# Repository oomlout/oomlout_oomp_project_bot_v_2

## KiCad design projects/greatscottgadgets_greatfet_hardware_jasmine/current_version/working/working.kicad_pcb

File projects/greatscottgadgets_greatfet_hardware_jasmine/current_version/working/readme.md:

# greatfet_hardware
 
## summary 
* id: greatscottgadgets_greatfet_hardware_jasmine
* user: greatscottgadgets
* name: greatfet_hardware
* board: jasmine
* repo: https://github.com/greatscottgadgets/greatfet-hardware
* src_file_repo_kicad_pcb: jasmine/jasmine.kicad_pcb
* src_file_repo_kicad_pcb_link: https://github.com/greatscottgadgets/greatfet-hardware/tree/master/jasmine/jasmine.kicad_pcb

* src_file_repo_sch: jasmine/jasmine.sch
* src_file_repo_sch_link: https://github.com/greatscottgadgets/greatfet-hardware/tree/master/jasmine/jasmine.sch
* full details link: https://github.com/oomlout/oomlout_oomp_project_bot_v_2/tree/main/projects/greatscottgadgets_greatfet_hardware_jasmine/current_version/working

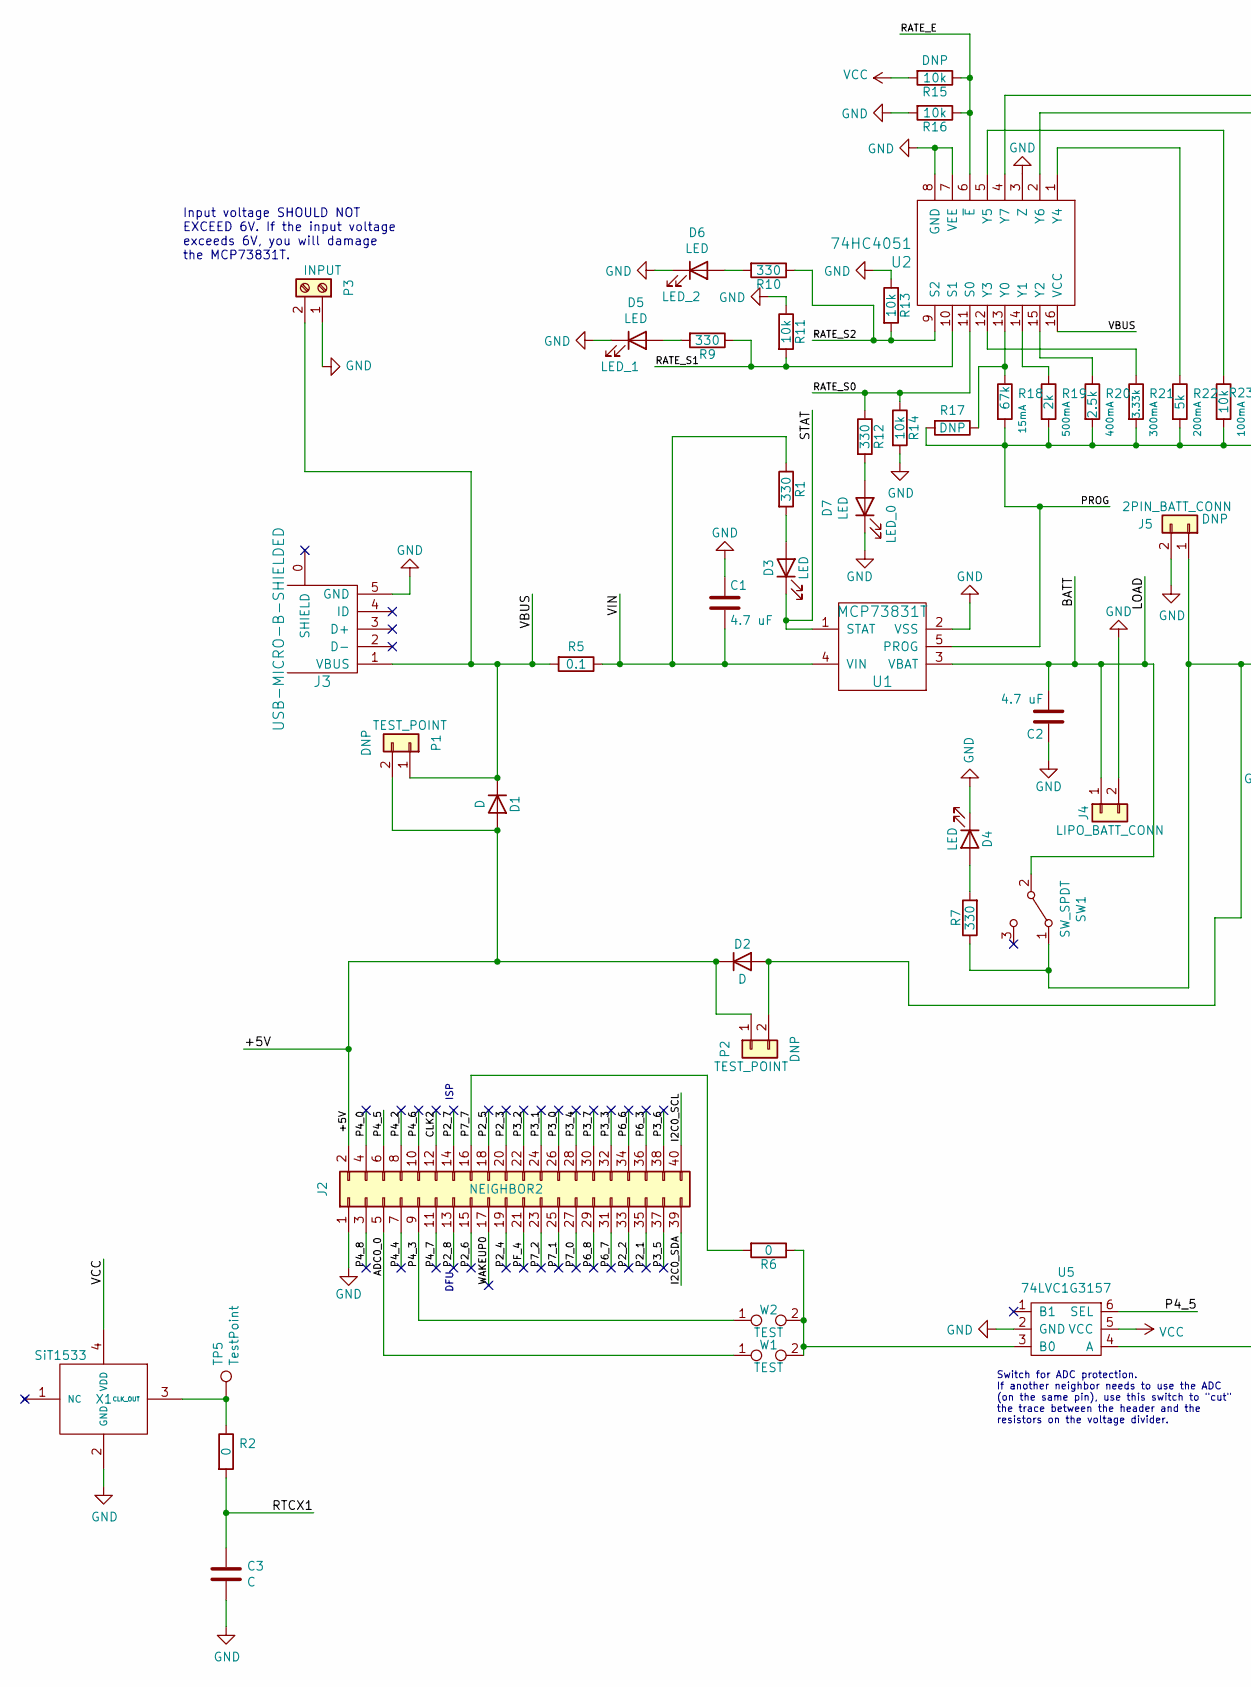
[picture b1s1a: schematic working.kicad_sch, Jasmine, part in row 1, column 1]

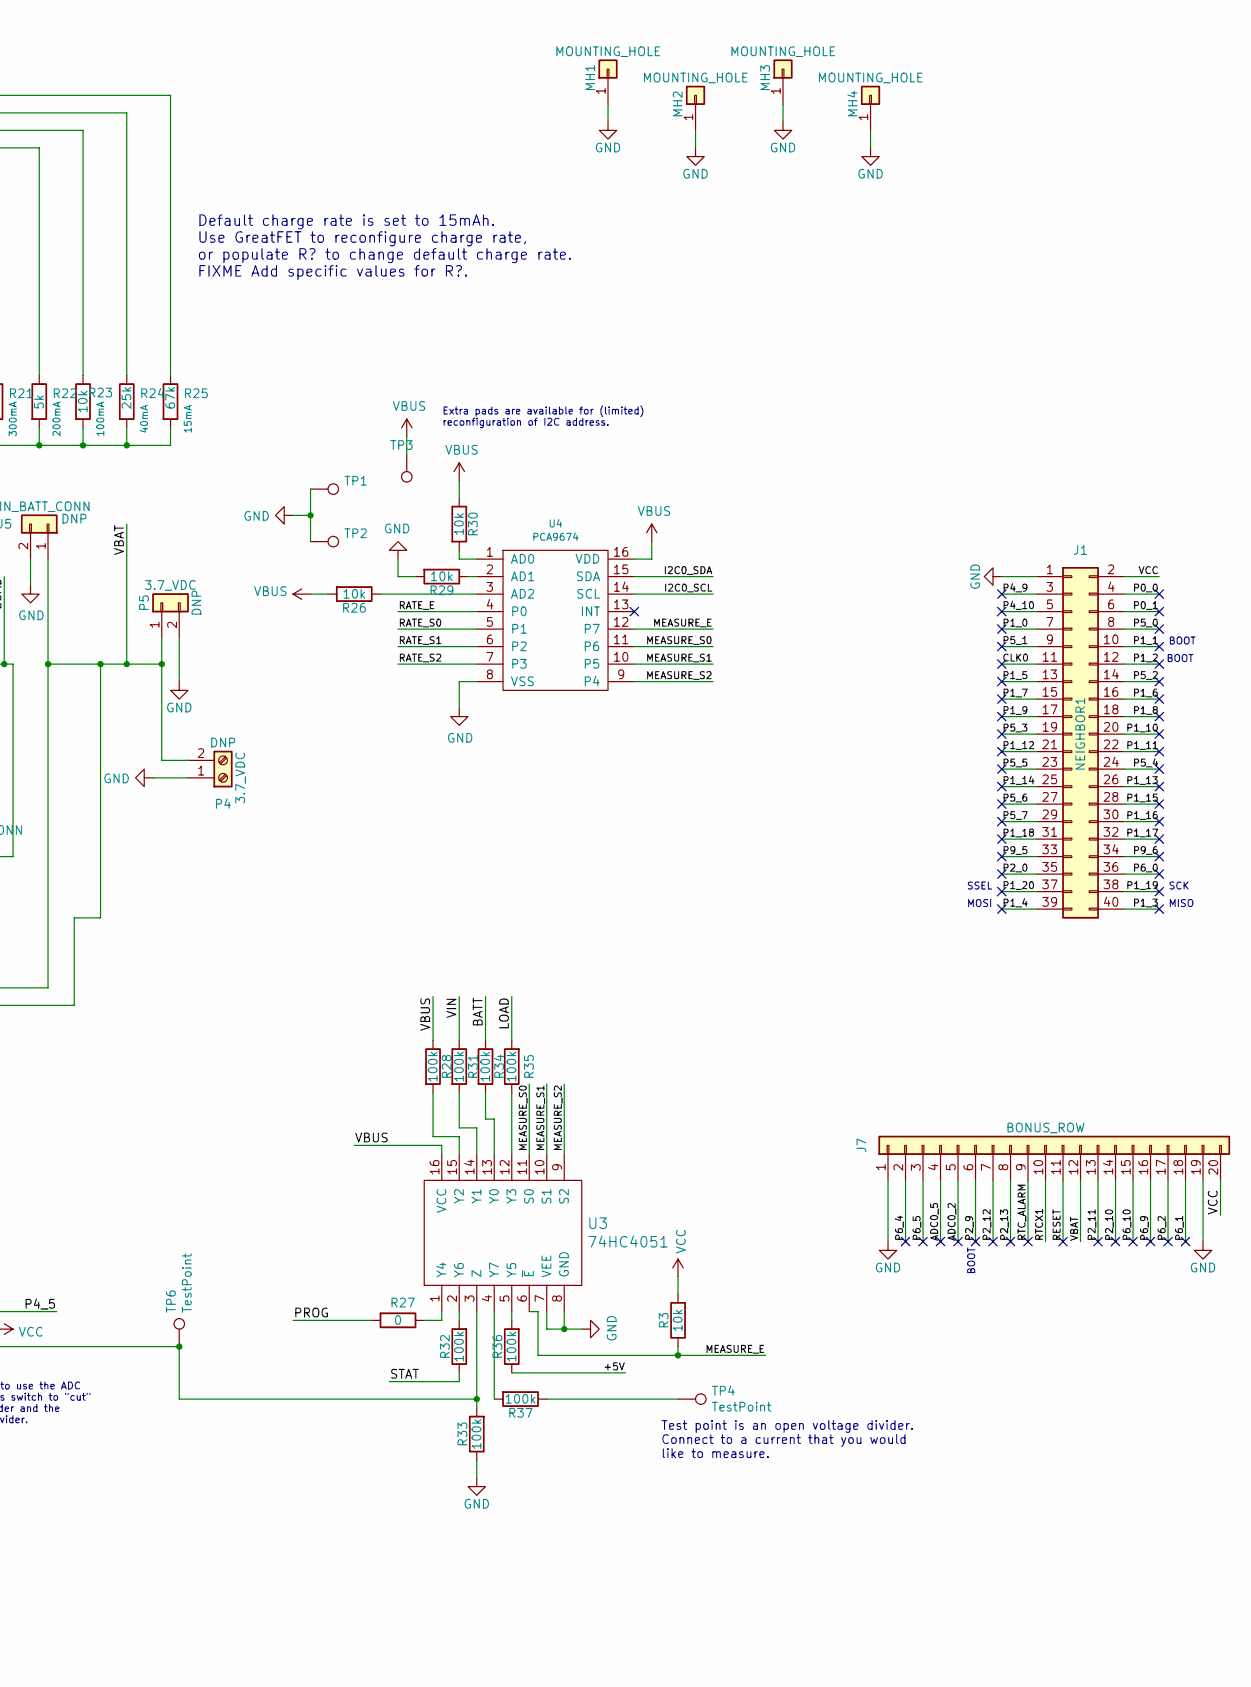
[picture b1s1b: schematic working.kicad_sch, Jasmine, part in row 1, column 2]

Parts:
C1, C2: 4.7 uF; 0603; Part Number GRM188R60J475KE19D
C3: C; 0603
D1, D2: D; SOD128; Part Number PMEG3050EP,115
D3: LED; 0603D; Part Number SML-LX0603GW-TR
D4: LED; 0603D; Part Number SML-LX0603IW-TR
D5, D6, D7: LED; 0603D; Part Number SML-D12Y8WT86
J1: NEIGHBOR1; HEADER-2x20; Part Number SSQ-120-23-G-D
J2: NEIGHBOR2; HEADER-2x20; Part Number SSQ-120-23-G-D
J3: USB-MICRO-B-SHIELDED; USB-MICROB-FCI-10103592-LONGPADS; Part Number 10103592-0001LF
J4: LIPO_BATT_CONN; JST_PH_S2B-PH-SM4-TB_02x2.00mm_Angled; Part Number S2B-PH-SM4-TB(LF)(SN)
J5: 2PIN_BATT_CONN; JST_PH_S2B-PH-SM4-TB_02x2.00mm_Angled; Part Number S2B-PH-SM4-TB(LF)(SN)
J7: BONUS_ROW; HEADER-1x20; Part Number SSQ-120-23-G-S
MH1, MH2, MH3, MH4: MOUNTING_HOLE; HOLE126MIL-COPPER
P1, P2: TEST_POINT; HEADER-1x2; Part Number TSW-102-07-F-S
P3: INPUT; TerminalBlock_4UCON_19963_02x3.5mm_Straight; Part Number OSTTE020104
P4: 3.7_VDC; TerminalBlock_4UCON_19963_02x3.5mm_Straight; Part Number OSTTE020104
P5: 3.7_VDC; HEADER-1x2
R1, R9, R10, R12: 330; 0603; Part Number RMCF0603FT330R
R2, R27: 0; 0603; Part Number RMCF0603ZT0R00
R3, R11, R13, R14, R15, R16, R23, R26, R29, R30: 10k; 0603; Part Number RNCP0603FTD10K0
R5: 0.1; 0603; Part Number ERJ-3RSFR10V
R6: 0; 0603; Part Number RC0603JR-070RL
R7: 330; 0603; Part Number RMCF0603JT330R
R17: R; RESISTOR-AXIAL-2.3x6.0mm
R18, R25: 67k; 0603; Part Number RMCF0603FT66K5
R19: 2k; 0603; Part Number RMCF0603FT2K00
R20: 2.5k; 0603; Part Number RMCF0603FT2K49
R21: 3.33k; 0603; Part Number RMCF0603FG3K32
R22: 5k; 0603; Part Number RMCF0603FT4K99
R24: 25k; 0603; Part Number RMCF0603FT24K9
R28, R31, R32, R33, R34, R35, R36, R37: 100k; 0603; Part Number RMCF0603FG100K
SW1: SW_SPDT; MHSS1105; Part Number MHSS1105
TP1, TP2, TP3: 1Pin_0603
TP4, TP5, TP6: TestPoint; TESTPOINT-50MIL
U1: MCP73831T; SOT-23-5; Part Number MCP73831T-2ACI/OT
U2, U3: 74HC4051; SOIC16; Part Number 74HC4051D,653
U4: PCA9674; TSSOP16; Part Number PCA9674PW,118
U5: 74LVC1G3157; SOT363; Part Number 74LVC1G3157DW-7
W1, W2: TEST; 0603-JUMPER
X1: SiT1533; Part Number SIT1533AI-H4-AA2-32.768G

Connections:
/+5V: D1.2 (A), D2.1 (K), J2.2, P1.2, P2.1, R36.1
/ADC0_0: J2.5, W1.1
/ADC0_2: J7.5
/ADC0_5: J7.4
/BATT: C2.2, J4.1, R34.1, R35.2, SW1.2 (B), U1.3 (VBAT)
/CLK0: J1.11
/CLK2: J2.12
/I2C0_SCL: J2.40, U4.14 (SCL)
/I2C0_SDA: J2.39, U4.15 (SDA)
/MEASURE_E: R3.1, U3.6 (~E), U4.12 (P7)
/MEASURE_S0: U3.11 (S0), U4.11 (P6)
/MEASURE_S1: U3.10 (S1), U4.10 (P5)
/MEASURE_S2: U3.9 (S2), U4.9 (P4)
/P0_0: J1.4
/P0_1: J1.6
/P1_0: J1.7
/P1_1: J1.10
/P1_2: J1.12
/P1_3: J1.40
/P1_4: J1.39
/P1_5: J1.13
/P1_6: J1.16
/P1_7: J1.15
/P1_8: J1.18
/P1_9: J1.17
/P1_10: J1.20
/P1_11: J1.22
/P1_12: J1.21
/P1_13: J1.26
/P1_14: J1.25
/P1_15: J1.28
/P1_16: J1.30
/P1_17: J1.32
/P1_18: J1.31
/P1_19: J1.38
/P1_20: J1.37
/P2_0: J1.35
/P2_1: J2.35
/P2_2: J2.33
/P2_3: J2.20
/P2_4: J2.19
/P2_5: J2.18
/P2_6: J2.15
/P2_7: J2.14
/P2_8: J2.13
/P2_9: J7.6
/P2_10: J7.14
/P2_11: J7.13
/P2_12: J7.7
/P2_13: J7.8
/P3_0: J2.26
/P3_1: J2.24
/P3_2: J2.22
/P3_3: J2.32
/P3_4: J2.28
/P3_5: J2.37
/P3_6: J2.38
/P3_7: J2.30
/P4_0: J2.4
/P4_2: J2.8
/P4_3: J2.9, W2.1
/P4_4: J2.7
/P4_5: J2.6, U5.6 (SEL)
/P4_6: J2.10
/P4_7: J2.11
/P4_8: J2.3
/P4_9: J1.3
/P4_10: J1.5
/P5_0: J1.8
/P5_1: J1.9
/P5_2: J1.14
/P5_3: J1.19
/P5_4: J1.24
/P5_5: J1.23
/P5_6: J1.27
/P5_7: J1.29
/P6_0: J1.36
/P6_1: J7.18
/P6_2: J7.17
/P6_3: J2.36
/P6_4: J7.2
/P6_5: J7.3
/P6_6: J2.34
/P6_7: J2.31
/P6_8: J2.29
/P6_9: J7.16
/P6_10: J7.15
/P7_0: J2.27
/P7_1: J2.25
/P7_2: J2.23
/P7_7: J2.16, R6.2
/P9_5: J1.33
/P9_6: J1.34
/PF_4: J2.21
/PROG: R17.2, R18.2, R19.2, R20.2, R21.2, R22.2, R23.2, R24.2, R25.2, R27.2, U1.5 (PROG)
/RATE_E: R15.1, R16.1, U2.6 (~E), U4.4 (P0)
/RATE_S0: R12.1, R14.1, U2.11 (S0), U4.5 (P1)
/RATE_S1: R9.1, R11.2, U2.10 (S1), U4.6 (P2)
/RATE_S2: R10.1, R13.2, U2.9 (S2), U4.7 (P3)
/RESET: J7.11
/RTCX1: C3.1, J7.10, R2.2
/RTC_ALARM: J7.9
/STAT: D3.1 (K), R32.1, U1.1 (STAT)
/VBAT: D2.2 (A), J5.1, J7.12, P2.2, P4.2, P5.1, R7.1, SW1.1 (A)
/VIN: C1.2, R1.1, R5.1, R31.1, U1.4 (VIN)
/WAKEUP0: J2.17
GND: C1.1, C2.1, C3.2, D4.1 (K), D5.1 (K), D6.1 (K), D7.1 (K), J1.1, J2.1, J3.5 (GND), J4.2, J5.2, J7.1, J7.19, MH1.1, MH2.1, MH3.1, MH4.1, P3.1, P4.1, P5.2, R11.1, R13.1, R14.2, R16.2, R29.2, R33.1, TP1.1, TP2.1, U1.2 (VSS), U2.3 (Z), U2.7 (VEE), U2.8 (GND), U3.7 (VEE), U3.8 (GND), U4.8 (VSS), U5.2 (GND), X1.2 (GND)
unnamed: D3.2 (A), R1.2
unnamed: D4.2 (A), R7.2
unnamed: D5.2 (A), R9.2
unnamed: D6.2 (A), R10.2
unnamed: D7.2 (A), R12.2
unnamed: R2.1, TP5.1, X1.3 (CLK_OUT)
unnamed: R6.1, U5.3 (B0), W1.2, W2.2
unnamed: R17.1, R18.1, U2.13 (Y0)
unnamed: R19.1, U2.14 (Y1)
unnamed: R20.1, U2.15 (Y2)
unnamed: R21.1, U2.12 (Y3)
unnamed: R22.1, U2.1 (Y4)
unnamed: R23.1, U2.5 (Y5)
unnamed: R24.1, U2.2 (Y6)
unnamed: R25.1, U2.4 (Y7)
unnamed: R26.1, U4.3 (AD2)
unnamed: R27.1, U3.1 (Y4)
unnamed: R28.2, U3.15 (Y2)
unnamed: R29.1, U4.2 (AD1)
unnamed: R30.2, U4.1 (AD0)
unnamed: R31.2, U3.14 (Y1)
unnamed: R32.2, U3.2 (Y6)
unnamed: R33.2, TP6.1, U3.3 (Z), U5.4 (A)
unnamed: R34.2, U3.13 (Y0)
unnamed: R35.1, U3.12 (Y3)
unnamed: R36.2, U3.5 (Y5)
unnamed: R37.1, TP4.1
unnamed: R37.2, U3.4 (Y7)
VBUS: D1.1 (K), J3.1 (VBUS), P1.1, P3.2, R5.2, R26.2, R28.1, R30.1, TP3.1, U2.16 (VCC), U3.16 (VCC), U4.16 (VDD)
VCC: J1.2, J7.20, R3.2, R15.2, U5.5 (VCC), X1.4 (VDD)

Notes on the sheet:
Input voltage SHOULD NOT EXCEED 6V. If the input voltage exceeds 6V, you will damage the MCP73831T.
Default charge rate is set to 15mAh. Use GreatFET to reconfigure charge rate, or populate R? to change default charge rate. FIXME Add specific values for R?.
Extra pads are available for (limited) reconfiguration of I2C address.
Switch for ADC protection. If another neighbor needs to use the ADC (on the same pin), use this switch to "cut" the trace between the header and the resistors on the voltage divider.
MISO
SCK
Test point is an open voltage divider. Connect to a current that you would like to measure.
BOOT
MOSI
ISP
DFU
SSEL

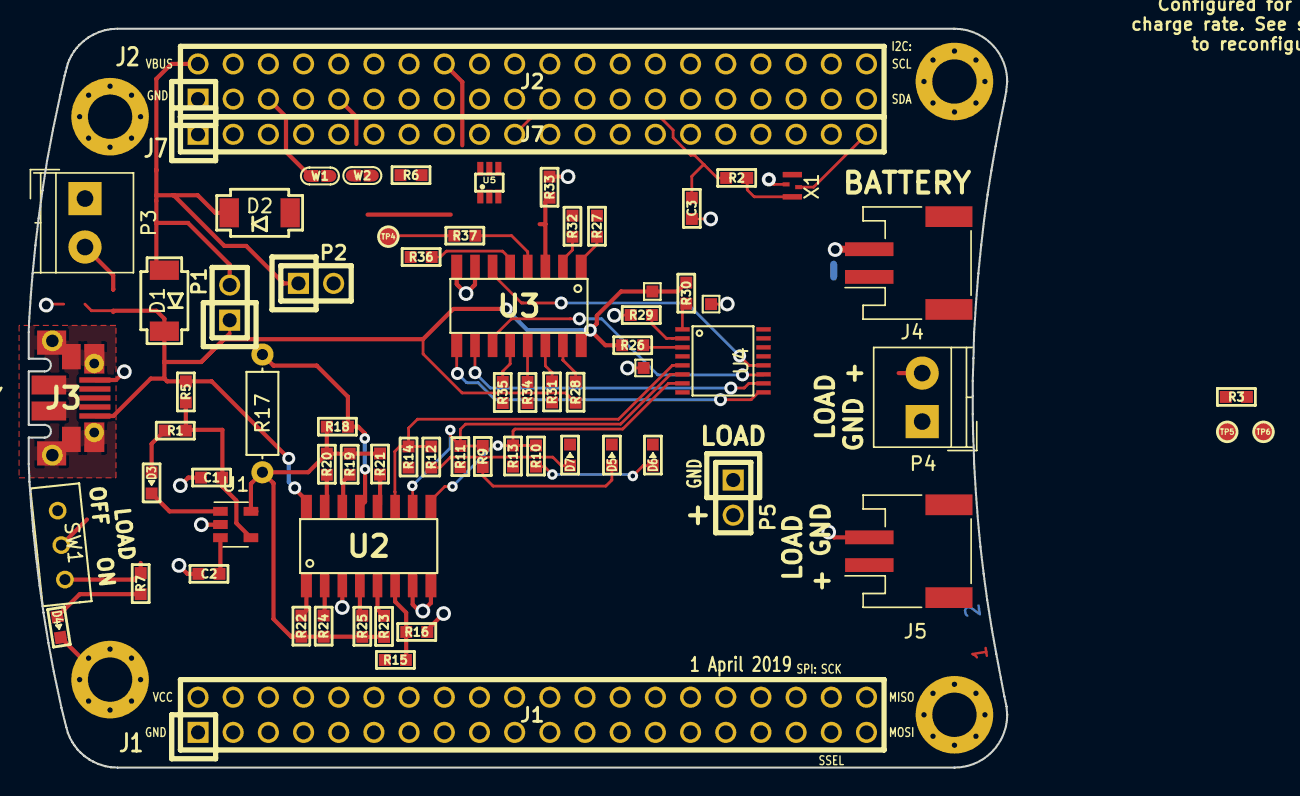
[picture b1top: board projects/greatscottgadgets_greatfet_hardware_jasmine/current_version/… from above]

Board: 2 copper layers, 70.6 x 53.3 mm, 75 parts (0 on the bottom side), 52 nets.

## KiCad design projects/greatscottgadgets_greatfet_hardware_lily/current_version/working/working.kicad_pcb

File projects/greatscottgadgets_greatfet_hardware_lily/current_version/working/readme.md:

# greatfet_hardware
 
## summary 
* id: greatscottgadgets_greatfet_hardware_lily
* user: greatscottgadgets
* name: greatfet_hardware
* board: lily
* repo: https://github.com/greatscottgadgets/greatfet-hardware
* src_file_repo_kicad_pcb: lily/lily.kicad_pcb
* src_file_repo_kicad_pcb_link: https://github.com/greatscottgadgets/greatfet-hardware/tree/master/lily/lily.kicad_pcb

* src_file_repo_sch: lily/lily.sch
* src_file_repo_sch_link: https://github.com/greatscottgadgets/greatfet-hardware/tree/master/lily/lily.sch
* full details link: https://github.com/oomlout/oomlout_oomp_project_bot_v_2/tree/main/projects/greatscottgadgets_greatfet_hardware_lily/current_version/working

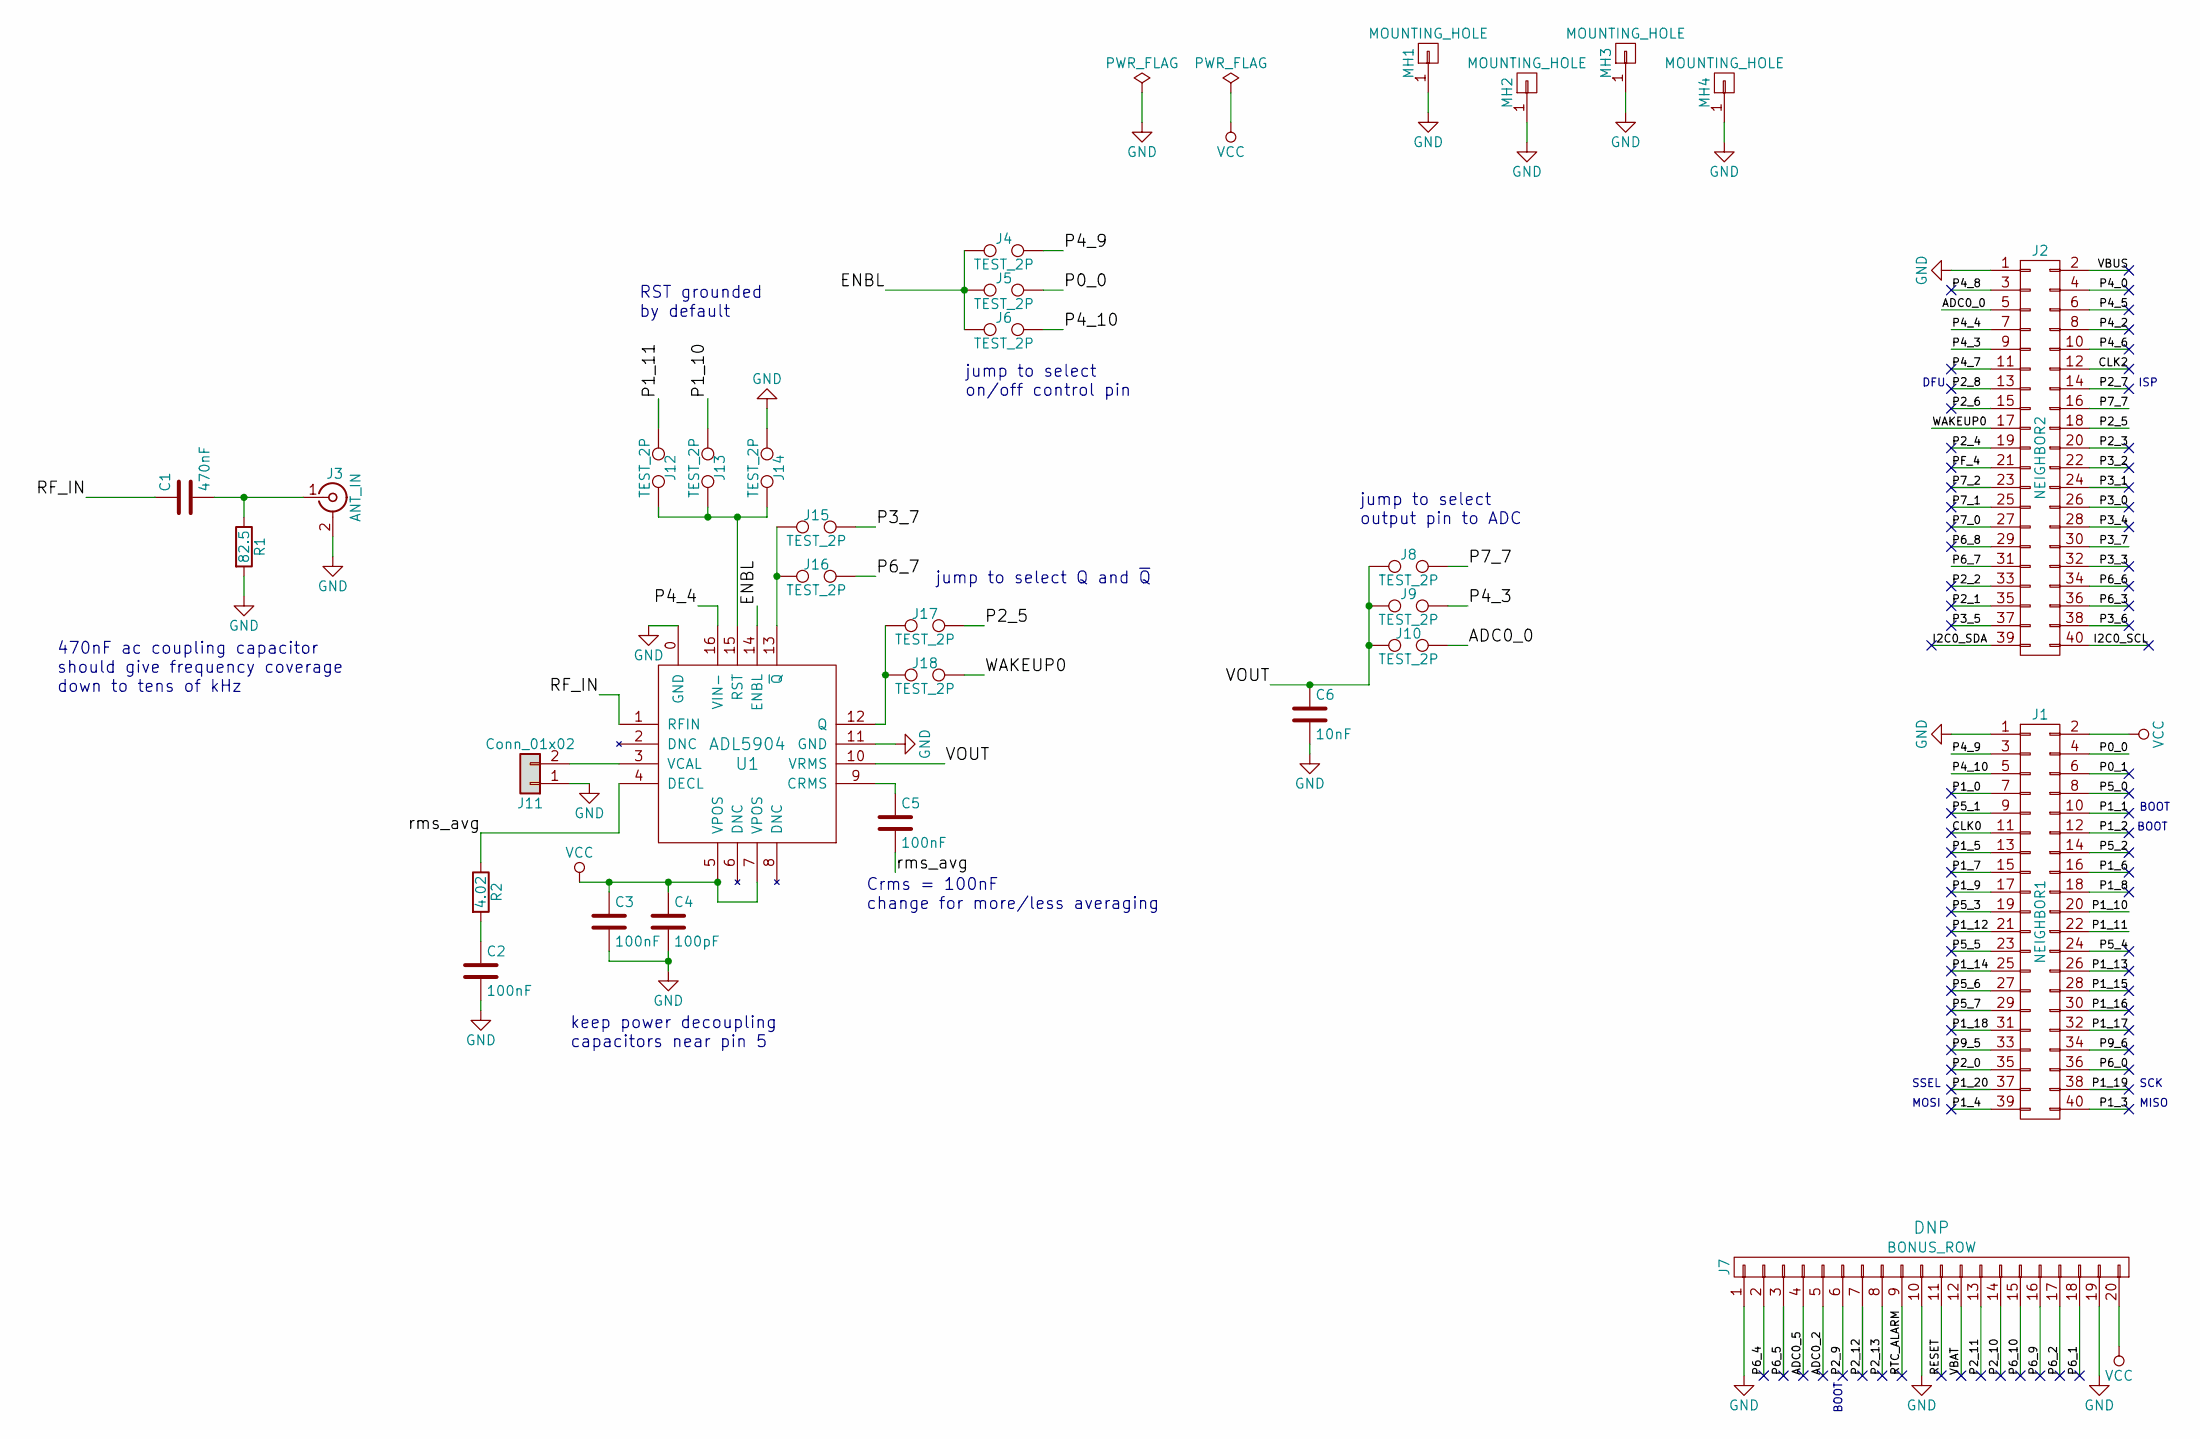
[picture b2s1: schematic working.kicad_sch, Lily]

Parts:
C1: 470nF; 0603; Part Number GRM188R61H474KA12D
C2, C3, C5: 100nF; 0603; Part Number GCM188L81H104KA57D
C4: 100pF; 0603; Part Number GQM1885C1H101JB01D
C6: 10nF; 0603; Part Number 885012206065
J1: NEIGHBOR1; HEADER-2x20; Part Number SSQ-120-23-G-D
J2: NEIGHBOR2; HEADER-2x20; Part Number SSQ-120-23-G-D
J3: ANT_IN; SMA-EDGE; Part Number CONREVSMA003.031
J4, J5, J6, J8, J9, J10, J12, J13, J14, J15, J16, J17, J18: TEST_2P; 0603-JUMPER
J7: BONUS_ROW; HEADER-1x20; Part Number SSQ-120-23-G-S
J11: Conn_01x02; Pin_Header_Straight_1x02_Pitch2.54mm
MH1, MH2, MH3, MH4: MOUNTING_HOLE; HOLE126MIL-COPPER
R1: 82.5; 0603; Part Number RMCF0603FT82R5
R2: 4.02; 0603; Part Number RMCF0603FT4R02
U1: ADL5904; QFN16-3; Part Number ADL5904ACPZN-R7

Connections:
/ADC0_0: J2.5, J10.2
/ADC0_2: J7.5
/ADC0_5: J7.4
/CLK0: J1.11
/CLK2: J2.12
/ENBL: J4.1, J5.1, J6.1, U1.14 (ENBL)
/I2C0_SCL: J2.40
/I2C0_SDA: J2.39
/P0_0: J1.4, J5.2
/P0_1: J1.6
/P1_0: J1.7
/P1_1: J1.10
/P1_2: J1.12
/P1_3: J1.40
/P1_4: J1.39
/P1_5: J1.13
/P1_6: J1.16
/P1_7: J1.15
/P1_8: J1.18
/P1_9: J1.17
/P1_10: J1.20, J13.1
/P1_11: J1.22, J12.1
/P1_12: J1.21
/P1_13: J1.26
/P1_14: J1.25
/P1_15: J1.28
/P1_16: J1.30
/P1_17: J1.32
/P1_18: J1.31
/P1_19: J1.38
/P1_20: J1.37
/P2_0: J1.35
/P2_1: J2.35
/P2_2: J2.33
/P2_3: J2.20
/P2_4: J2.19
/P2_5: J2.18, J17.2
/P2_6: J2.15
/P2_7: J2.14
/P2_8: J2.13
/P2_9: J7.6
/P2_10: J7.14
/P2_11: J7.13
/P2_12: J7.7
/P2_13: J7.8
/P3_0: J2.26
/P3_1: J2.24
/P3_2: J2.22
/P3_3: J2.32
/P3_4: J2.28
/P3_5: J2.37
/P3_6: J2.38
/P3_7: J2.30, J15.2
/P4_0: J2.4
/P4_2: J2.8
/P4_3: J2.9, J9.2
/P4_4: J2.7, U1.16 (VIN-)
/P4_5: J2.6
/P4_6: J2.10
/P4_7: J2.11
/P4_8: J2.3
/P4_9: J1.3, J4.2
/P4_10: J1.5, J6.2
/P5_0: J1.8
/P5_1: J1.9
/P5_2: J1.14
/P5_3: J1.19
/P5_4: J1.24
/P5_5: J1.23
/P5_6: J1.27
/P5_7: J1.29
/P6_0: J1.36
/P6_1: J7.18
/P6_2: J7.17
/P6_3: J2.36
/P6_4: J7.2
/P6_5: J7.3
/P6_6: J2.34
/P6_7: J2.31, J16.2
/P6_8: J2.29
/P6_9: J7.16
/P6_10: J7.15
/P7_0: J2.27
/P7_1: J2.25
/P7_2: J2.23
/P7_7: J2.16, J8.2
/P9_5: J1.33
/P9_6: J1.34
/PF_4: J2.21
/RESET: J7.11
/RF_IN: C1.1, U1.1 (RFIN)
/RTC_ALARM: J7.9
/VBAT: J7.12
/VBUS: J2.2
/VOUT: C6.1, J8.1, J9.1, J10.1, U1.10 (VRMS)
/WAKEUP0: J2.17, J18.2
/rms_avg: C5.2, R2.1, U1.4 (DECL)
GND: C2.2, C3.2, C4.2, C6.2, J1.1, J2.1, J3.2 (Ext), J7.1, J7.10, J7.19, J11.1, J14.1, MH1.1, MH2.1, MH3.1, MH4.1, R1.2, U1.0 (GND), U1.11 (GND)
unnamed: C1.2, J3.1 (In), R1.1
unnamed: C2.1, R2.2
unnamed: C5.1, U1.9 (CRMS)
unnamed: J11.2, U1.3 (VCAL)
unnamed: J12.2, J13.2, J14.2, U1.15 (RST)
unnamed: J15.1, J16.1, U1.13 (~Q)
unnamed: J17.1, J18.1, U1.12 (Q)
VCC: C3.1, C4.1, J1.2, J7.20, U1.5 (VPOS), U1.7 (VPOS)

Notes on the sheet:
BOOT
jump to select on/off control pin
jump to select output pin to ADC
MISO
keep power decoupling capacitors near pin 5
jump to select Q and ~{Q}
SSEL
470nF ac coupling capacitor should give frequency coverage down to tens of kHz
MOSI
RST grounded by default
ISP
Crms = 100nF change for more/less averaging
DFU
SCK

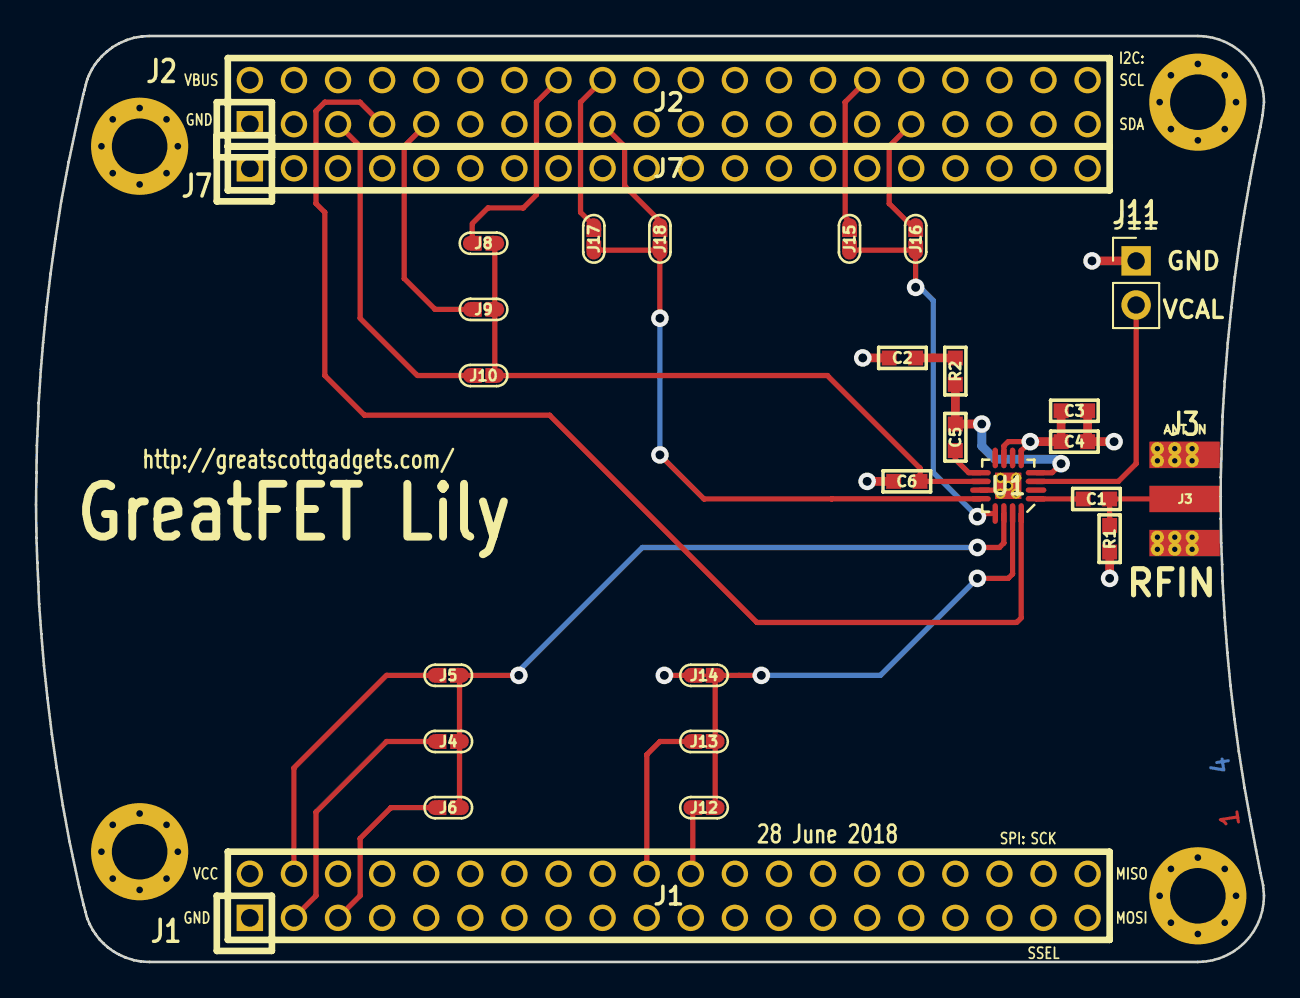
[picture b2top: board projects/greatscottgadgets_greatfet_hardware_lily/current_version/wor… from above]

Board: 4 copper layers, 70.7 x 53.3 mm, 31 parts (0 on the bottom side), 26 nets.

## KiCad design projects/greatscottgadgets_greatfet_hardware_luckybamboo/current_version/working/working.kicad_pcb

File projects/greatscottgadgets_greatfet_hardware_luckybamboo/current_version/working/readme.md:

# greatfet_hardware
 
## summary 
* id: greatscottgadgets_greatfet_hardware_luckybamboo
* user: greatscottgadgets
* name: greatfet_hardware
* board: luckybamboo
* repo: https://github.com/greatscottgadgets/greatfet-hardware
* src_file_repo_kicad_pcb: luckybamboo/luckybamboo.kicad_pcb
* src_file_repo_kicad_pcb_link: https://github.com/greatscottgadgets/greatfet-hardware/tree/master/luckybamboo/luckybamboo.kicad_pcb

* src_file_repo_sch: luckybamboo/luckybamboo.sch
* src_file_repo_sch_link: https://github.com/greatscottgadgets/greatfet-hardware/tree/master/luckybamboo/luckybamboo.sch
* full details link: https://github.com/oomlout/oomlout_oomp_project_bot_v_2/tree/main/projects/greatscottgadgets_greatfet_hardware_luckybamboo/current_version/working

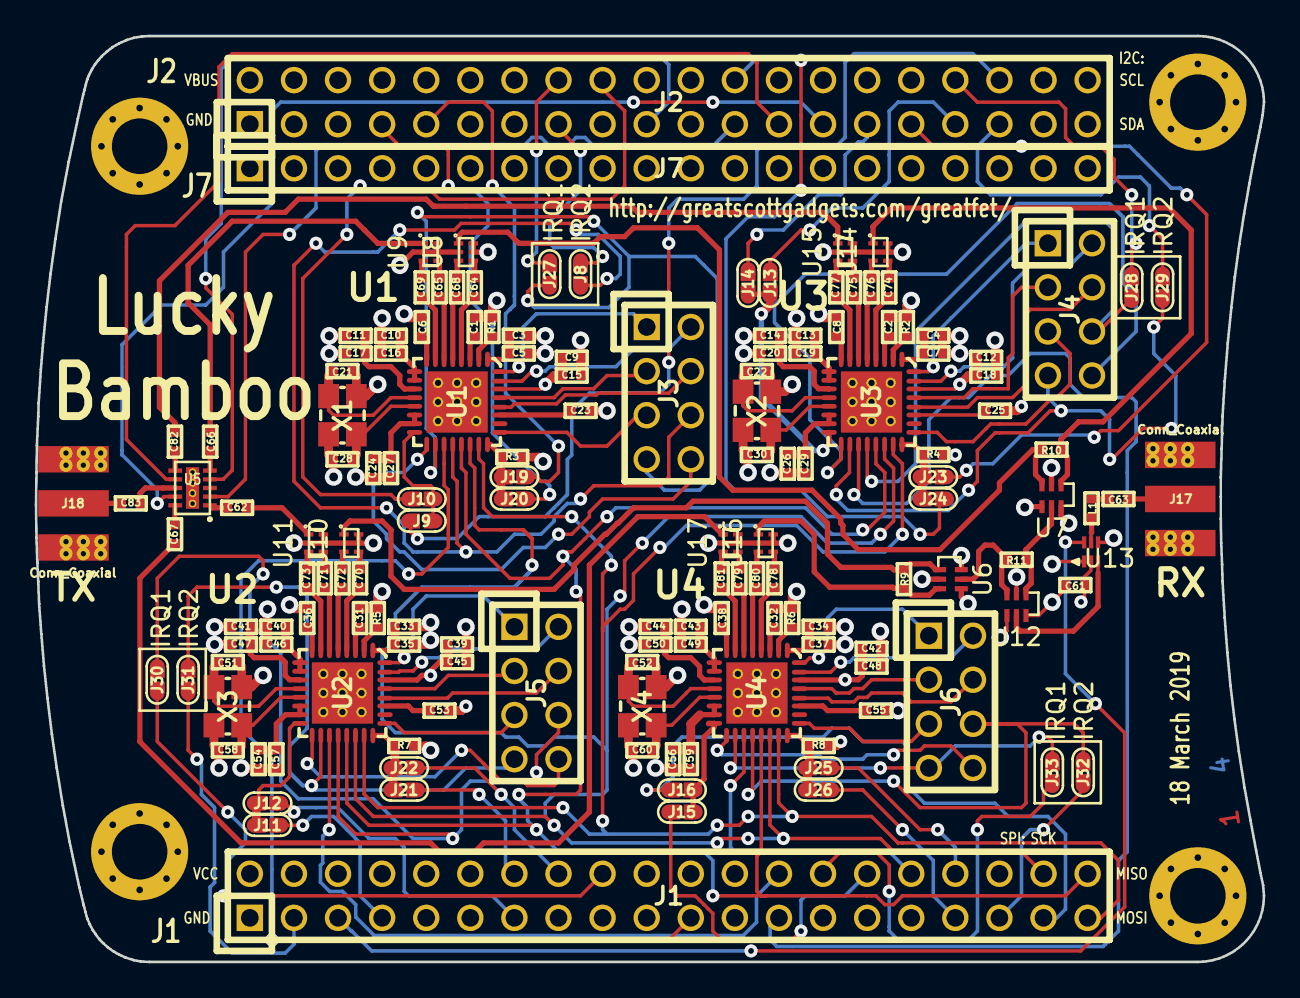
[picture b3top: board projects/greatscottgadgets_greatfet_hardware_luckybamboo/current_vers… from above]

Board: 4 copper layers, 70.7 x 53.3 mm, 153 parts (0 on the bottom side), 170 nets.

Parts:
C1, C2, C6, C8, C31, C32, C36, C38: 100pF; 0402
C3, C4, C9, C10, C11, C12, C13, C14, C24, C26, C33, C34, C39, C40, C41, C42, C43, C44, C54, C56: 220nF; 0402
C5, C7, C15, C16, C17, C18, C19, C20, C27, C29, C35, C37, C45, C46, C47, C48, C49, C50, C57, C59: 27pF; 0402
C21, C22, C28, C30, C51, C52, C58, C60: 18pF; 0402
C23, C25, C53, C55, C61, C63: 1nF; 0402
C62, C66, C67, C82, C83: 47pF; 0402
C64, C65, C68, C69, C70, C71, C72, C73, C74, C75, C76, C77, C78, C79, C80, C81: 10nF; 0402
J1: NEIGHBOR1; HEADER-2x20
J2: NEIGHBOR2; HEADER-2x20
J3, J4, J5, J6: Conn_01x08; HEADER-2x4
J7: BONUS_ROW; HEADER-1x20
J8, J9, J10, J11, J12, J13, J14, J15, J16, J19, J20, J21, J22, J23, J24, J25, J26, J27, J28, J29, J30, J31, J32, J33: TEST_2P; 0603-JUMPER
J17, J18: Conn_Coaxial; SMA-EDGE
L1: 3.8nH; 0402
MH1, MH2, MH3, MH4: MOUNTING_HOLE; HOLE126MIL-COPPER
R1, R2, R5, R6: 27k; 0402
R3, R4, R7, R8: 10k; 0402
R9, R10, R11: 100; 0402
U1, U2, U3, U4: ADF7242; LFCSP32
U5: SKY13322; SKY13322-375LF
U6, U7, U12: HHM2293A1
U8, U9, U10, U11, U14, U15, U16, U17: ADF7242_balun
U13: BGA7H1N6
X1, X2, X3, X4: XTAL4PIN; XTAL3.2x2.5mm

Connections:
/DR1: J9.1, J10.1, U1.16
/DR2: J11.1, J12.1, U2.16
/DR3: J13.1, J14.1, U3.16
/DR4: J15.1, J16.1, U4.16
/DT1: J3.8, U1.17
/DT2: J5.8, U2.17
/DT3: J4.8, U3.17
/DT4: J6.8, U4.17
/IRQ1: J3.6, J8.2, U1.20
/IRQ2: J5.6, J30.2, U2.20
/IRQ3: J4.6, J28.2, U3.20
/IRQ4: J6.6, J32.2, U4.20
/P1_0: J1.7, J11.2
/P1_3: J1.40, U1.21, U2.21, U3.21, U4.21
/P1_4: J1.39, U1.23, U2.23, U3.23, U4.23
/P1_5: J1.13, J12.2
/P1_6: J1.16, J22.2
/P1_8: J1.18, J30.1
/P1_12: J1.21, U1.19
/P1_13: J1.26, U2.19
/P1_14: J1.25, U3.19
/P1_15: J1.28, J33.1
/P1_16: J1.30, J15.2
/P1_17: J1.32, U4.19
/P1_19: J1.38, U1.22, U2.22, U3.22, U4.22
/P1_20: J1.37, J16.2
/P2_0: J1.35, J32.1
/P2_1: J2.35, J29.1
/P2_2: J2.33, J13.2
/P2_4: J2.19, U5.4
/P2_5: J2.18, J10.2
/P2_6: J2.15, J8.1
/P3_1: J2.24, J24.2
/P4_3: J2.9, J19.2
/P4_4: J2.7, J20.2
/P4_9: J1.3, J31.1
/P4_10: J1.5, U13.6
/P5_2: J1.14, J21.2
/P6_3: J2.36, J9.2
/P6_6: J2.34, J28.1
/P6_7: J2.31, J23.2
/P6_8: J2.29, J14.2
/P7_0: J2.27, U5.9
/P7_1: J2.25, U5.7
/P7_2: J2.23, U5.2
/P7_7: J2.16, J27.1
/P9_5: J1.33, J26.2
/P9_6: J1.34, J25.2
/PABIAOP1: J3.1, U1.32
/PABIAOP2: J5.1, U2.32
/PABIAOP3: J4.1, U3.32
/PABIAOP4: J6.1, U4.32
/PAVSUP1: J3.2, U1.31
/PAVSUP2: J5.2, U2.31
/PAVSUP3: J4.2, U3.31
/PAVSUP4: J6.2, U4.31
/RFIN: L1.1, U13.5
/RFIN1: R10.1, U7.3, U8.1
/RFIN1_N: C68.2, U1.5
/RFIN1_P: C64.2, U1.4
/RFIN2: R9.2, U6.1, U10.1
/RFIN2_N: C72.2, U2.5
/RFIN2_P: C70.2, U2.4
/RFIN3: R10.2, U7.1, U14.1
/RFIN3_N: C76.2, U3.5
/RFIN3_P: C74.2, U3.4
/RFIN4: R9.1, U6.3, U16.1
/RFIN4_N: C80.2, U4.5
/RFIN4_P: C78.2, U4.4
/RFOUT1: C66.2, U9.1
/RFOUT1_N: C69.2, U1.7
/RFOUT1_P: C65.2, U1.6
/RFOUT2: C62.1, U11.1
/RFOUT2_N: C73.2, U2.7
/RFOUT2_P: C71.2, U2.6
/RFOUT3: C82.1, U15.1
/RFOUT3_N: C77.2, U3.7
/RFOUT3_P: C75.2, U3.6
/RFOUT4: C67.2, U17.1
/RFOUT4_N: C81.2, U4.7
/RFOUT4_P: C79.2, U4.6
/TRFS1: J3.7, J27.2, U1.18
/TRFS2: J5.7, J31.2, U2.18
/TRFS3: J4.7, J29.2, U3.18
/TRFS4: J6.7, J33.2, U4.18
/TXEN1: J3.5, U1.25
/TXEN2: J5.5, U2.25
/TXEN3: J4.5, U3.25
/TXEN4: J6.5, U4.25
/XOSC32KN1: J3.3, U1.29
/XOSC32KN2: J5.3, U2.29
/XOSC32KN3: J4.3, U3.29
/XOSC32KN4: J6.3, U4.29
/XOSC32KP1: J3.4, U1.28
/XOSC32KP2: J5.4, U2.28
/XOSC32KP3: J4.4, U3.28
/XOSC32KP4: J6.4, U4.28
/~CS1: J19.1, J20.1, R3.2, U1.24
/~CS2: J21.1, J22.1, R7.2, U2.24
/~CS3: J23.1, J24.1, R4.2, U3.24
/~CS4: J25.1, J26.1, R8.2, U4.24
GND: C1.1, C2.1, C3.1, C4.1, C5.1, C6.2, C7.1, C8.2, C9.1, C10.2, C11.2, C12.1, C13.2, C14.2, C15.1, C16.2, C17.2, C18.1, C19.2, C20.2, C21.2, C22.2, C23.1, C24.2, C25.1, C26.2, C27.2, C28.2, C29.2, C30.2, C31.1, C32.1, C33.1, C34.1, C35.1, C36.2, C37.1, C38.2, C39.1, C40.2, C41.2, C42.1, C43.2, C44.2, C45.1, C46.2, C47.2, C48.1, C49.2, C50.2, C51.2, C52.2, C53.1, C54.2, C55.1, C56.2, C57.2, C58.2, C59.2, C60.2, C61.1, J1.1, J2.1, J7.1, J7.10, J7.19, J17.2, J18.2, MH1.1, MH2.1, MH3.1, MH4.1, R1.1, R2.1, R5.1, R6.1, U1.0, U2.0, U3.0, U4.0, U5.0, U6.2, U6.4, U6.6, U7.2, U7.4, U7.6, U8.2, U8.5, U8.6, U9.2, U9.5, U9.6, U10.2, U10.5, U10.6, U11.2, U11.5, U11.6, U12.2, U12.4, U12.6, U13.1, U13.4, U14.2, U14.5, U14.6, U15.2, U15.5, U15.6, U16.2, U16.5, U16.6, U17.2, U17.5, U17.6, X1.2, X1.4, X2.2, X2.4, X3.2, X3.4, X4.2, X4.4
unnamed: C1.2, U1.3
unnamed: C2.2, U3.3
unnamed: C3.2, C5.2, U1.1
unnamed: C4.2, C7.2, U3.1
unnamed: C6.1, U1.8
unnamed: C8.1, U3.8
unnamed: C10.1, C16.1, U1.9, U1.10
unnamed: C11.1, C17.1, U1.11
unnamed: C13.1, C19.1, U3.9, U3.10
unnamed: C14.1, C20.1, U3.11
unnamed: C21.1, U1.12, X1.1
unnamed: C22.1, U3.12, X2.1
unnamed: C23.2, U1.27
unnamed: C24.1, C27.1, U1.14, U1.15
unnamed: C25.2, U3.27
unnamed: C26.1, C29.1, U3.14, U3.15
unnamed: C28.1, U1.13, X1.3
unnamed: C30.1, U3.13, X2.3
unnamed: C31.2, U2.3
unnamed: C32.2, U4.3
unnamed: C33.2, C35.2, U2.1
unnamed: C34.2, C37.2, U4.1
unnamed: C36.1, U2.8
unnamed: C38.1, U4.8
unnamed: C40.1, C46.1, U2.9, U2.10
unnamed: C41.1, C47.1, U2.11
unnamed: C43.1, C49.1, U4.9, U4.10
unnamed: C44.1, C50.1, U4.11
unnamed: C51.1, U2.12, X3.1
unnamed: C52.1, U4.12, X4.1
unnamed: C53.2, U2.27
unnamed: C54.1, C57.1, U2.14, U2.15
unnamed: C55.2, U4.27
unnamed: C56.1, C59.1, U4.14, U4.15
unnamed: C58.1, U2.13, X3.3
unnamed: C60.1, U4.13, X4.3
unnamed: C62.2, U5.1
unnamed: C63.1, L1.2
unnamed: C63.2, J17.1
unnamed: C64.1, U8.4
unnamed: C65.1, U9.4
unnamed: C66.1, U5.5
unnamed: C67.1, U5.10
unnamed: C68.1, U8.3
unnamed: C69.1, U9.3
unnamed: C70.1, U10.4
unnamed: C71.1, U11.4
unnamed: C72.1, U10.3
unnamed: C73.1, U11.3
unnamed: C74.1, U14.4
unnamed: C75.1, U15.4
unnamed: C76.1, U14.3
unnamed: C77.1, U15.3
unnamed: C78.1, U16.4
unnamed: C79.1, U17.4
unnamed: C80.1, U16.3
unnamed: C81.1, U17.3
unnamed: C82.2, U5.6
unnamed: C83.1, U5.8
unnamed: C83.2, J18.1
unnamed: R1.2, U1.2
unnamed: R2.2, U3.2
unnamed: R5.2, U2.2
unnamed: R6.2, U4.2
unnamed: R11.1, U6.5, U12.3
unnamed: R11.2, U7.5, U12.1
unnamed: U12.5, U13.3
VCC: C9.2, C12.2, C15.2, C18.2, C39.2, C42.2, C45.2, C48.2, C61.2, J1.2, J7.20, R3.1, R4.1, R7.1, R8.1, U1.30, U2.30, U3.30, U4.30, U13.2

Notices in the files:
projects/greatscottgadgets_greatfet_hardware_jasmine/current_version/working/working.kicad_sch:
Copyright 2015 Michael Ossmann
License: GPL v2
projects/greatscottgadgets_greatfet_hardware_narcissus/current_version/working/working.kicad_pcb:
Copyright 2018 Great Scott Gadgets
License: BSD-3-Clause
projects/greatscottgadgets_greatfet_hardware_neighbor_template/current_version/working/working.kicad_sch:
Copyright 2015 Great Scott Gadgets
projects/greatscottgadgets_greatfet_hardware_quince/current_version/working/working.kicad_sch:
Copyright 2019 Great Scott Gadgets
